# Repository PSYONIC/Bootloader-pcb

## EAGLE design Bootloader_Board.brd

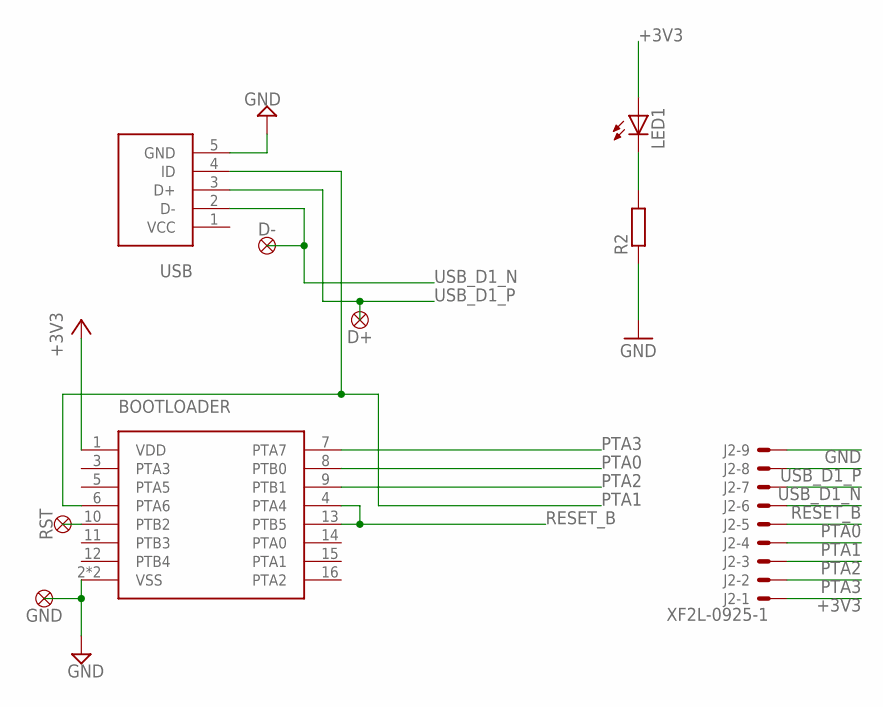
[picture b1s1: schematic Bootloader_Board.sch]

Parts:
BOOTLOADER: MKL02Z32CORRECT; QFN16
D+: TESTPAD
D-: TESTPAD
GND: TESTPAD
J2: XF2L-0925-1
LED1: LED_ESML0603; LED_SML0603
R2: RR0603; R0603
RST: TESTPAD
USB: 10118194-0001LF

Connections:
+3V3: BOOTLOADER.1 (VDD), J2.1 (MSV), LED1.A
GND: BOOTLOADER.2 (VSS), BOOTLOADER.TH (VSS), GND.P$1, J2.9 (MS), R2.1, USB.5 (GND)
unnamed: BOOTLOADER.10 (PTB2), RST.P$1
unnamed: LED1.C, R2.2
PTA0: BOOTLOADER.8 (PTB0), J2.5 (MS)
PTA1: BOOTLOADER.6 (PTA6), J2.4 (MS), USB.4 (ID)
PTA2: BOOTLOADER.9 (PTB1), J2.3 (MS)
PTA3: BOOTLOADER.7 (PTA7), J2.2 (MS)
RESET_B: BOOTLOADER.4 (PTA4), BOOTLOADER.13 (PTB5), J2.6 (MS)
USB_D1_N: D-.P$1, J2.7 (MS), USB.2 (D-)
USB_D1_P: D+.P$1, J2.8 (MS), USB.3 (D+)

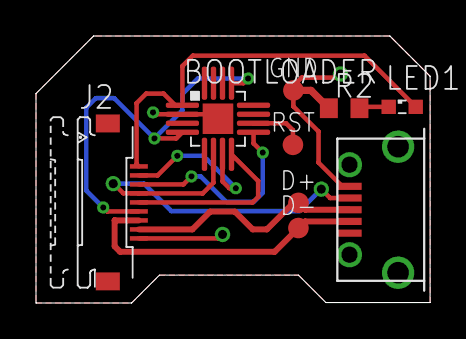
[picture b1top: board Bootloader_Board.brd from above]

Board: 2 copper layers, 21.9 x 14.8 mm, 9 parts (0 on the bottom side), 11 nets.

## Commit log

2016-10-07 first
    first commit
2016-10-07 readme
    added readme
